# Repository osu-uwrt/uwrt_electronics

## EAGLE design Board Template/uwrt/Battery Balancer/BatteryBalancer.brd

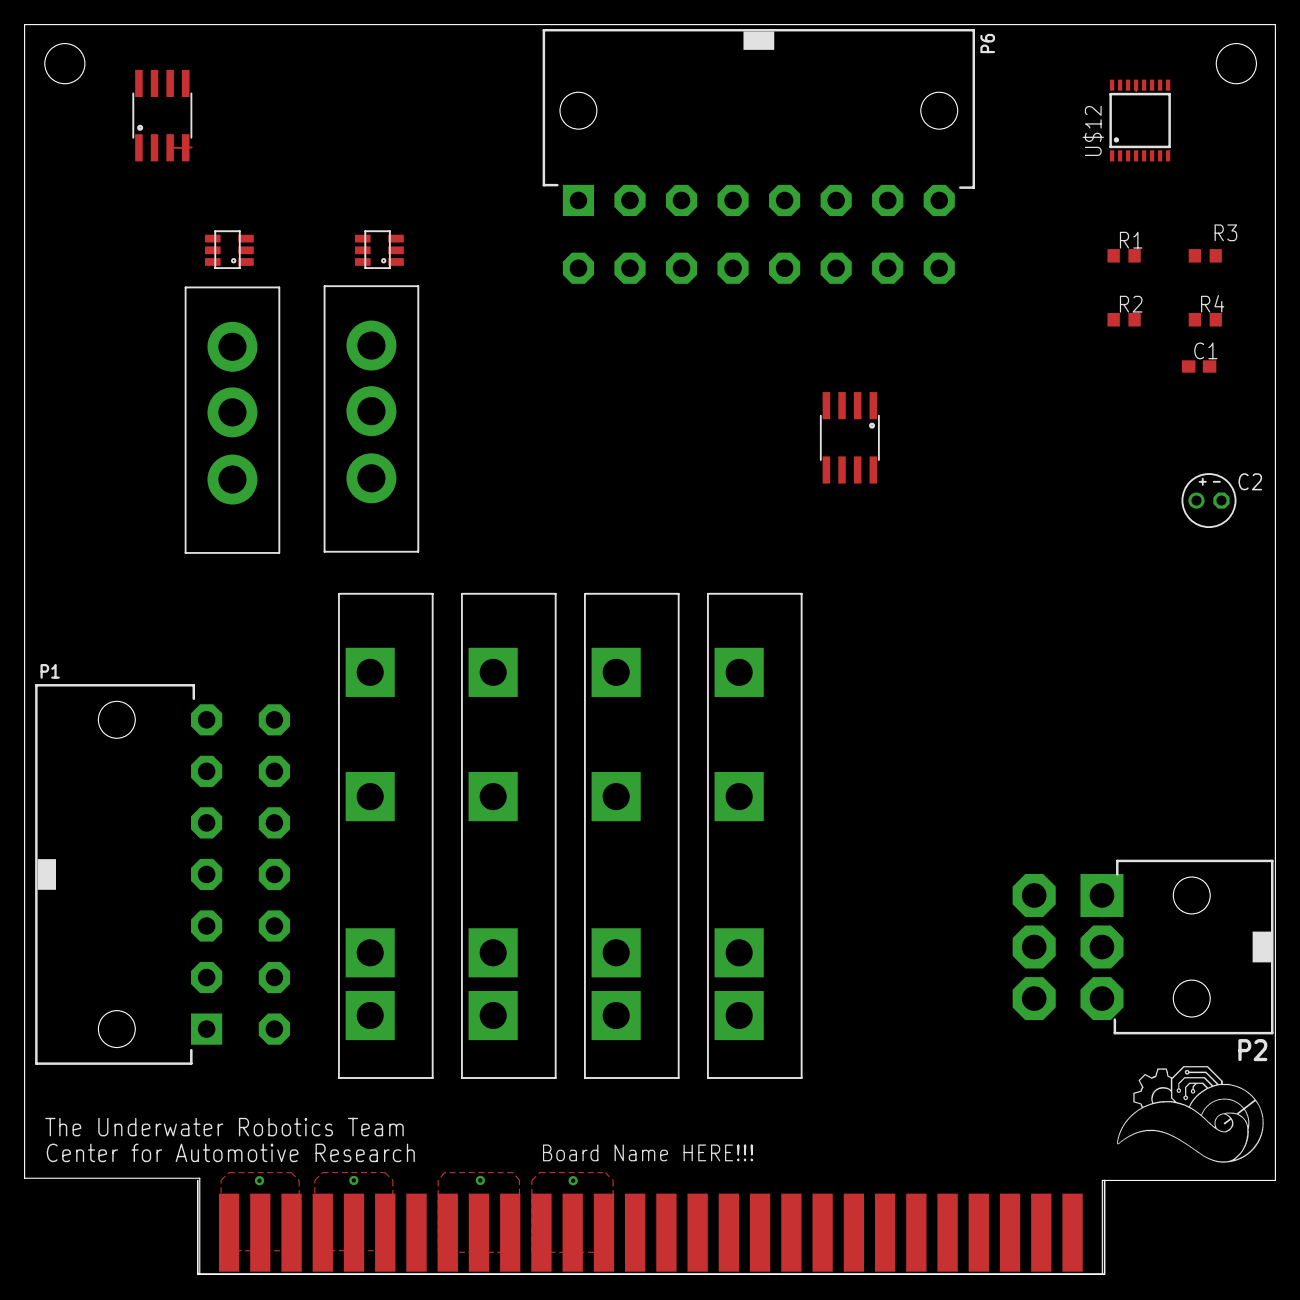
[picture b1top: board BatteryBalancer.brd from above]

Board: 2 copper layers, 101.7 x 101.6 mm, 21 parts (0 on the bottom side), 21 nets.

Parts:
C1: C0603
C2: E2-4
P1: 39-30-14?; 39-30-?14?
P2: 39-30-06?; 39-30-?06?
P6: 39-30-16?; 39-30-?16?
R1, R2, R3, R4: 100K; R0603
U$1: 5530843-EDGE; 5530843-6-BOARDFINGERS
U$2, U$3: LM5050
U$4, U$5: IXFX64N60P3
U$6, U$7: ACS722; SOIC-8
U$8, U$9, U$10, U$11: CMX60D20
U$12: ADC128D818; TSSOP-16

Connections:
+3V3: C1.1, C2.+, U$1.1, U$1.2, U$1.3, U$1.54, U$1.55, U$1.56, U$6.VCC, U$7.VCC, U$12.VREF
+5V: U$1.11, U$1.12, U$1.13, U$1.44, U$1.45, U$1.46
BALANCED_OUT: P2.1, P2.2, P2.3, U$2.1, U$2.6, U$3.1, U$3.6, U$4.DRAIN, U$5.DRAIN
GND: P1.8, P1.9, P1.10, P1.11, P1.12, P1.13, P1.14, P2.4, P2.5, P2.6, P6.9, P6.10, P6.11, P6.12, P6.13, P6.14, P6.15, P6.16, U$1.4, U$1.5, U$1.6, U$1.8, U$1.9, U$1.10, U$1.47, U$1.48, U$1.49, U$1.51, U$1.52, U$1.53, U$2.2, U$3.2, U$6.BW_SEL, U$6.GND, U$7.BW_SEL, U$7.GND, U$8.CONTROL-, U$9.CONTROL-, U$10.CONTROL-, U$11.CONTROL-
GNDA: C1.2, C2.-, R3.2, R4.2, U$12.GND
KILL_SWITCH: U$1.37, U$8.CONTROL+, U$9.CONTROL+, U$10.CONTROL+, U$11.CONTROL+
LOAD: U$8.LOAD+, U$9.LOAD+, U$10.LOAD+, U$11.LOAD+
MOTOR_POWER: P1.1, P1.2, P1.3, P1.4, P1.5, P1.6, P1.7, U$8.LOAD-, U$9.LOAD-
MOTOR_POWER2: U$10.LOAD-, U$11.LOAD-
unnamed: U$2.4, U$4.SOURCE, U$6.IP-1, U$6.IP-2
unnamed: U$2.5, U$4.GATE
unnamed: U$3.4, U$5.SOURCE, U$7.IP-1, U$7.IP-2
unnamed: U$3.5, U$5.GATE
unnamed: R1.2, R3.1, U$12.A0
unnamed: R1.1, R2.1, R2.2, R4.1, U$12.A1, U$12.V+
PORT_BATTERY: P6.5, P6.6, P6.7, P6.8, U$6.IP+1, U$6.IP+2
PORT_CURRENT: U$6.VIOUT, U$12.IN0
SENSOR_SCL: U$1.29, U$12.SCL
SENSOR_SDA: U$1.30, U$12.SDA
STBD_BATTERY: P6.1, P6.2, P6.3, P6.4, U$7.IP+1, U$7.IP+2
STBD_CURRENT: U$7.VIOUT, U$12.IN3

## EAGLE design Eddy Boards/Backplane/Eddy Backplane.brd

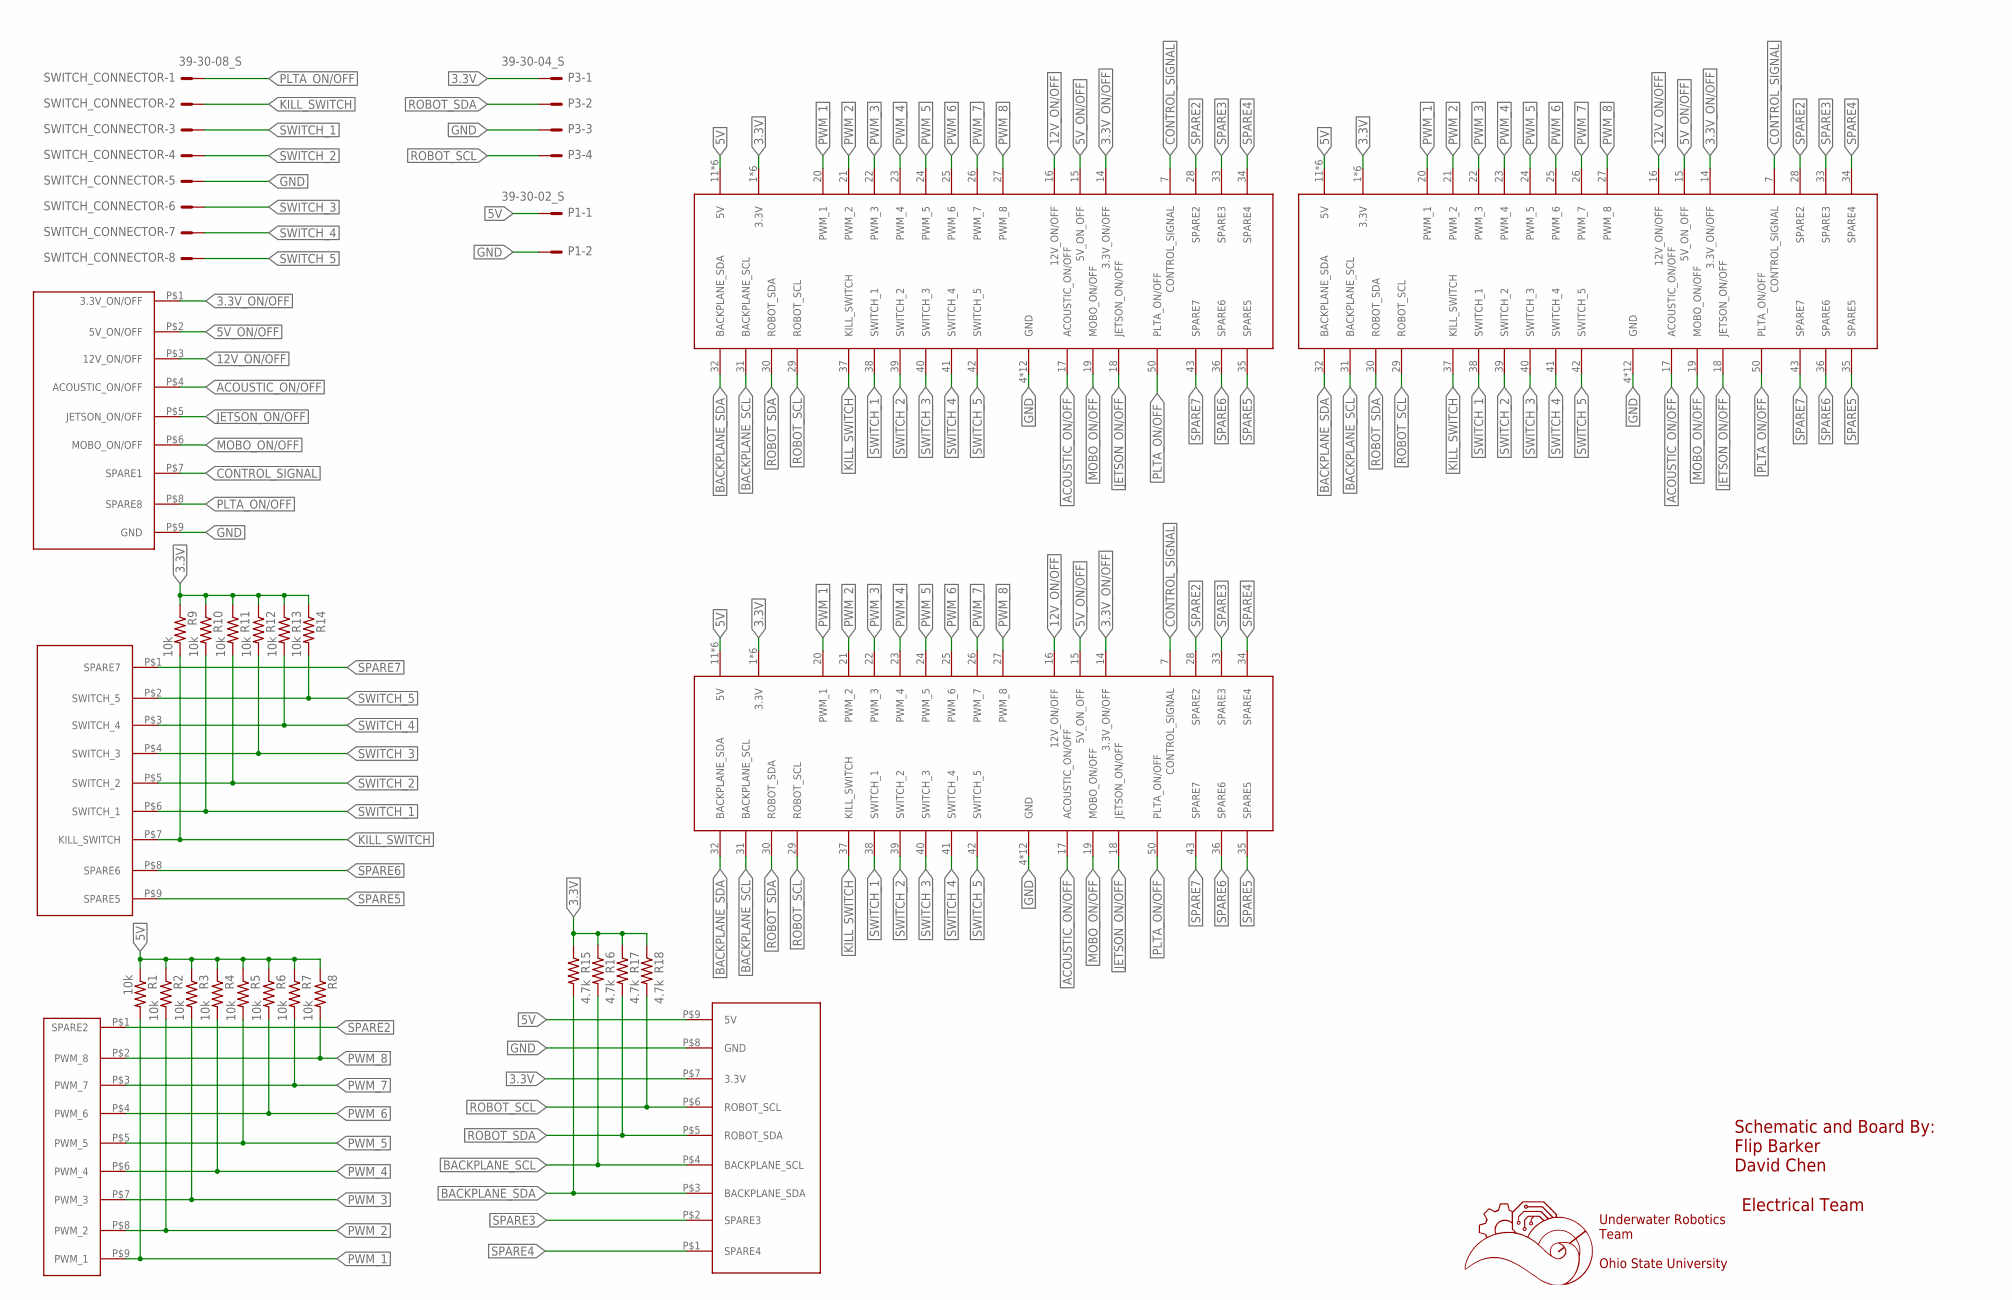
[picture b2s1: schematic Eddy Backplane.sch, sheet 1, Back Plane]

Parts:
P1: 39-30-02_S; 39-30-?02?
P3: 39-30-04_S; 39-30-?04?
PWR_ON: 929870-01-09_3; 929852-01-09_1ROW
R1, R2, R3, R4, R5, R6, R7, R8, R9, R10, R11, R12, R13, R14: 10k; R0603
R15, R16, R17, R18: 4.7k; R0603
SWITCH_CONN: 929870-01-09_1; 929852-01-09_1ROW
SWITCH_CONNECTOR: 39-30-08_S; 39-30-?08?
U$1, U$2, U$3: 5530843-FEMALE; 5530843-6-BACKPLANEMATE
U$6: 929870-01-09_2; 929852-01-09_1ROW
U$8: 929870-01-09_4; 929852-01-09_1ROW

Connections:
3.3V: P3.1, R9.1, R10.1, R11.1, R12.1, R13.1, R14.1, R15.1, R16.1, R17.1, R18.1, U$1.1 (3.3V), U$1.2 (3.3V), U$1.3 (3.3V), U$1.54 (3.3V), U$1.55 (3.3V), U$1.56 (3.3V), U$2.1 (3.3V), U$2.2 (3.3V), U$2.3 (3.3V), U$2.54 (3.3V), U$2.55 (3.3V), U$2.56 (3.3V), U$3.1 (3.3V), U$3.2 (3.3V), U$3.3 (3.3V), U$3.54 (3.3V), U$3.55 (3.3V), U$3.56 (3.3V), U$8.P$7 (3.3V); also elsewhere on the board
3.3V_ON/OFF: PWR_ON.P$1 (3.3V_ON/OFF), U$1.14 (3.3V_ON/OFF), U$2.14 (3.3V_ON/OFF), U$3.14 (3.3V_ON/OFF)
5V: P1.1, R1.1, R2.1, R3.1, R4.1, R5.1, R6.1, R7.1, R8.1, U$1.11 (5V), U$1.12 (5V), U$1.13 (5V), U$1.44 (5V), U$1.45 (5V), U$1.46 (5V), U$2.11 (5V), U$2.12 (5V), U$2.13 (5V), U$2.44 (5V), U$2.45 (5V), U$2.46 (5V), U$3.11 (5V), U$3.12 (5V), U$3.13 (5V), U$3.44 (5V), U$3.45 (5V), U$3.46 (5V), U$8.P$9 (5V); also elsewhere on the board
5V_ON/OFF: PWR_ON.P$2 (5V_ON/OFF), U$1.15 (5V_ON_OFF), U$2.15 (5V_ON_OFF), U$3.15 (5V_ON_OFF)
12V_ON/OFF: PWR_ON.P$3 (12V_ON/OFF), U$1.16 (12V_ON/OFF), U$2.16 (12V_ON/OFF), U$3.16 (12V_ON/OFF)
ACOUSTIC_ON/OFF: PWR_ON.P$4 (ACOUSTIC_ON/OFF), U$1.17 (ACOUSTIC_ON/OFF), U$2.17 (ACOUSTIC_ON/OFF), U$3.17 (ACOUSTIC_ON/OFF)
BACKPLANE_SCL: R16.2, U$1.31 (BACKPLANE_SCL), U$2.31 (BACKPLANE_SCL), U$3.31 (BACKPLANE_SCL), U$8.P$4 (BACKPLANE_SCL); also elsewhere on the board
BACKPLANE_SDA: R15.2, U$1.32 (BACKPLANE_SDA), U$2.32 (BACKPLANE_SDA), U$3.32 (BACKPLANE_SDA), U$8.P$3 (BACKPLANE_SDA); also elsewhere on the board
CONTROL_SIGNAL: PWR_ON.P$7 (SPARE1), U$1.7 (CONTROL_SIGNAL), U$2.7 (CONTROL_SIGNAL), U$3.7 (CONTROL_SIGNAL)
GND: P1.2, P3.3, PWR_ON.P$9 (GND), SWITCH_CONNECTOR.5, U$1.4 (GND), U$1.5 (GND), U$1.6 (GND), U$1.8 (GND), U$1.9 (GND), U$1.10 (GND), U$1.47 (GND), U$1.48 (GND), U$1.49 (GND), U$1.51 (GND), U$1.52 (GND), U$1.53 (GND), U$2.4 (GND), U$2.5 (GND), U$2.6 (GND), U$2.8 (GND), U$2.9 (GND), U$2.10 (GND), U$2.47 (GND), U$2.48 (GND), U$2.49 (GND), U$2.51 (GND), U$2.52 (GND), U$2.53 (GND), U$3.4 (GND), U$3.5 (GND), U$3.6 (GND), U$3.8 (GND), U$3.9 (GND), U$3.10 (GND), U$3.47 (GND), U$3.48 (GND), U$3.49 (GND), U$3.51 (GND), U$3.52 (GND), U$3.53 (GND), U$8.P$8 (GND); also elsewhere on the board
JETSON_ON/OFF: PWR_ON.P$5 (JETSON_ON/OFF), U$1.18 (JETSON_ON/OFF), U$2.18 (JETSON_ON/OFF), U$3.18 (JETSON_ON/OFF)
KILL_SWITCH: R9.2, SWITCH_CONN.P$7 (KILL_SWITCH), SWITCH_CONNECTOR.2, U$1.37 (KILL_SWITCH), U$2.37 (KILL_SWITCH), U$3.37 (KILL_SWITCH)
MOBO_ON/OFF: PWR_ON.P$6 (MOBO_ON/OFF), U$1.19 (MOBO_ON/OFF), U$2.19 (MOBO_ON/OFF), U$3.19 (MOBO_ON/OFF)
PLTA_ON/OFF: PWR_ON.P$8 (SPARE8), SWITCH_CONNECTOR.1, U$1.50 (PLTA_ON/OFF), U$2.50 (PLTA_ON/OFF), U$3.50 (PLTA_ON/OFF)
PWM_1: R1.2, U$1.20 (PWM_1), U$2.20 (PWM_1), U$3.20 (PWM_1), U$6.P$9 (PWM_1); also elsewhere on the board
PWM_2: R2.2, U$1.21 (PWM_2), U$2.21 (PWM_2), U$3.21 (PWM_2), U$6.P$8 (PWM_2); also elsewhere on the board
PWM_3: R3.2, U$1.22 (PWM_3), U$2.22 (PWM_3), U$3.22 (PWM_3), U$6.P$7 (PWM_3); also elsewhere on the board
PWM_4: R4.2, U$1.23 (PWM_4), U$2.23 (PWM_4), U$3.23 (PWM_4), U$6.P$6 (PWM_4); also elsewhere on the board
PWM_5: R5.2, U$1.24 (PWM_5), U$2.24 (PWM_5), U$3.24 (PWM_5), U$6.P$5 (PWM_5); also elsewhere on the board
PWM_6: R6.2, U$1.25 (PWM_6), U$2.25 (PWM_6), U$3.25 (PWM_6), U$6.P$4 (PWM_6); also elsewhere on the board
PWM_7: R7.2, U$1.26 (PWM_7), U$2.26 (PWM_7), U$3.26 (PWM_7), U$6.P$3 (PWM_7); also elsewhere on the board
PWM_8: R8.2, U$1.27 (PWM_8), U$2.27 (PWM_8), U$3.27 (PWM_8), U$6.P$2 (PWM_8); also elsewhere on the board
ROBOT_SCL: P3.4, R18.2, U$1.29 (ROBOT_SCL), U$2.29 (ROBOT_SCL), U$3.29 (ROBOT_SCL), U$8.P$6 (ROBOT_SCL); also elsewhere on the board
ROBOT_SDA: P3.2, R17.2, U$1.30 (ROBOT_SDA), U$2.30 (ROBOT_SDA), U$3.30 (ROBOT_SDA), U$8.P$5 (ROBOT_SDA); also elsewhere on the board
SPARE2: U$1.28 (SPARE2), U$2.28 (SPARE2), U$3.28 (SPARE2), U$6.P$1 (SPARE2)
SPARE3: U$1.33 (SPARE3), U$2.33 (SPARE3), U$3.33 (SPARE3), U$8.P$2 (SPARE3)
SPARE4: U$1.34 (SPARE4), U$2.34 (SPARE4), U$3.34 (SPARE4), U$8.P$1 (SPARE4)
SPARE5: SWITCH_CONN.P$9 (SPARE5), U$1.35 (SPARE5), U$2.35 (SPARE5), U$3.35 (SPARE5)
SPARE6: SWITCH_CONN.P$8 (SPARE6), U$1.36 (SPARE6), U$2.36 (SPARE6), U$3.36 (SPARE6)
SPARE7: SWITCH_CONN.P$1 (SPARE7), U$1.43 (SPARE7), U$2.43 (SPARE7), U$3.43 (SPARE7)
SWITCH_1: R10.2, SWITCH_CONN.P$6 (SWITCH_1), SWITCH_CONNECTOR.3, U$1.38 (SWITCH_1), U$2.38 (SWITCH_1), U$3.38 (SWITCH_1)
SWITCH_2: R11.2, SWITCH_CONN.P$5 (SWITCH_2), SWITCH_CONNECTOR.4, U$1.39 (SWITCH_2), U$2.39 (SWITCH_2), U$3.39 (SWITCH_2)
SWITCH_3: R12.2, SWITCH_CONN.P$4 (SWITCH_3), SWITCH_CONNECTOR.6, U$1.40 (SWITCH_3), U$2.40 (SWITCH_3), U$3.40 (SWITCH_3)
SWITCH_4: R13.2, SWITCH_CONN.P$3 (SWITCH_4), SWITCH_CONNECTOR.7, U$1.41 (SWITCH_4), U$2.41 (SWITCH_4), U$3.41 (SWITCH_4)
SWITCH_5: R14.2, SWITCH_CONN.P$2 (SWITCH_5), SWITCH_CONNECTOR.8, U$1.42 (SWITCH_5), U$2.42 (SWITCH_5), U$3.42 (SWITCH_5)

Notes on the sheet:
Underwater Robotics Team Ohio State University
Electrical Team
Schematic and Board By: Flip Barker David Chen

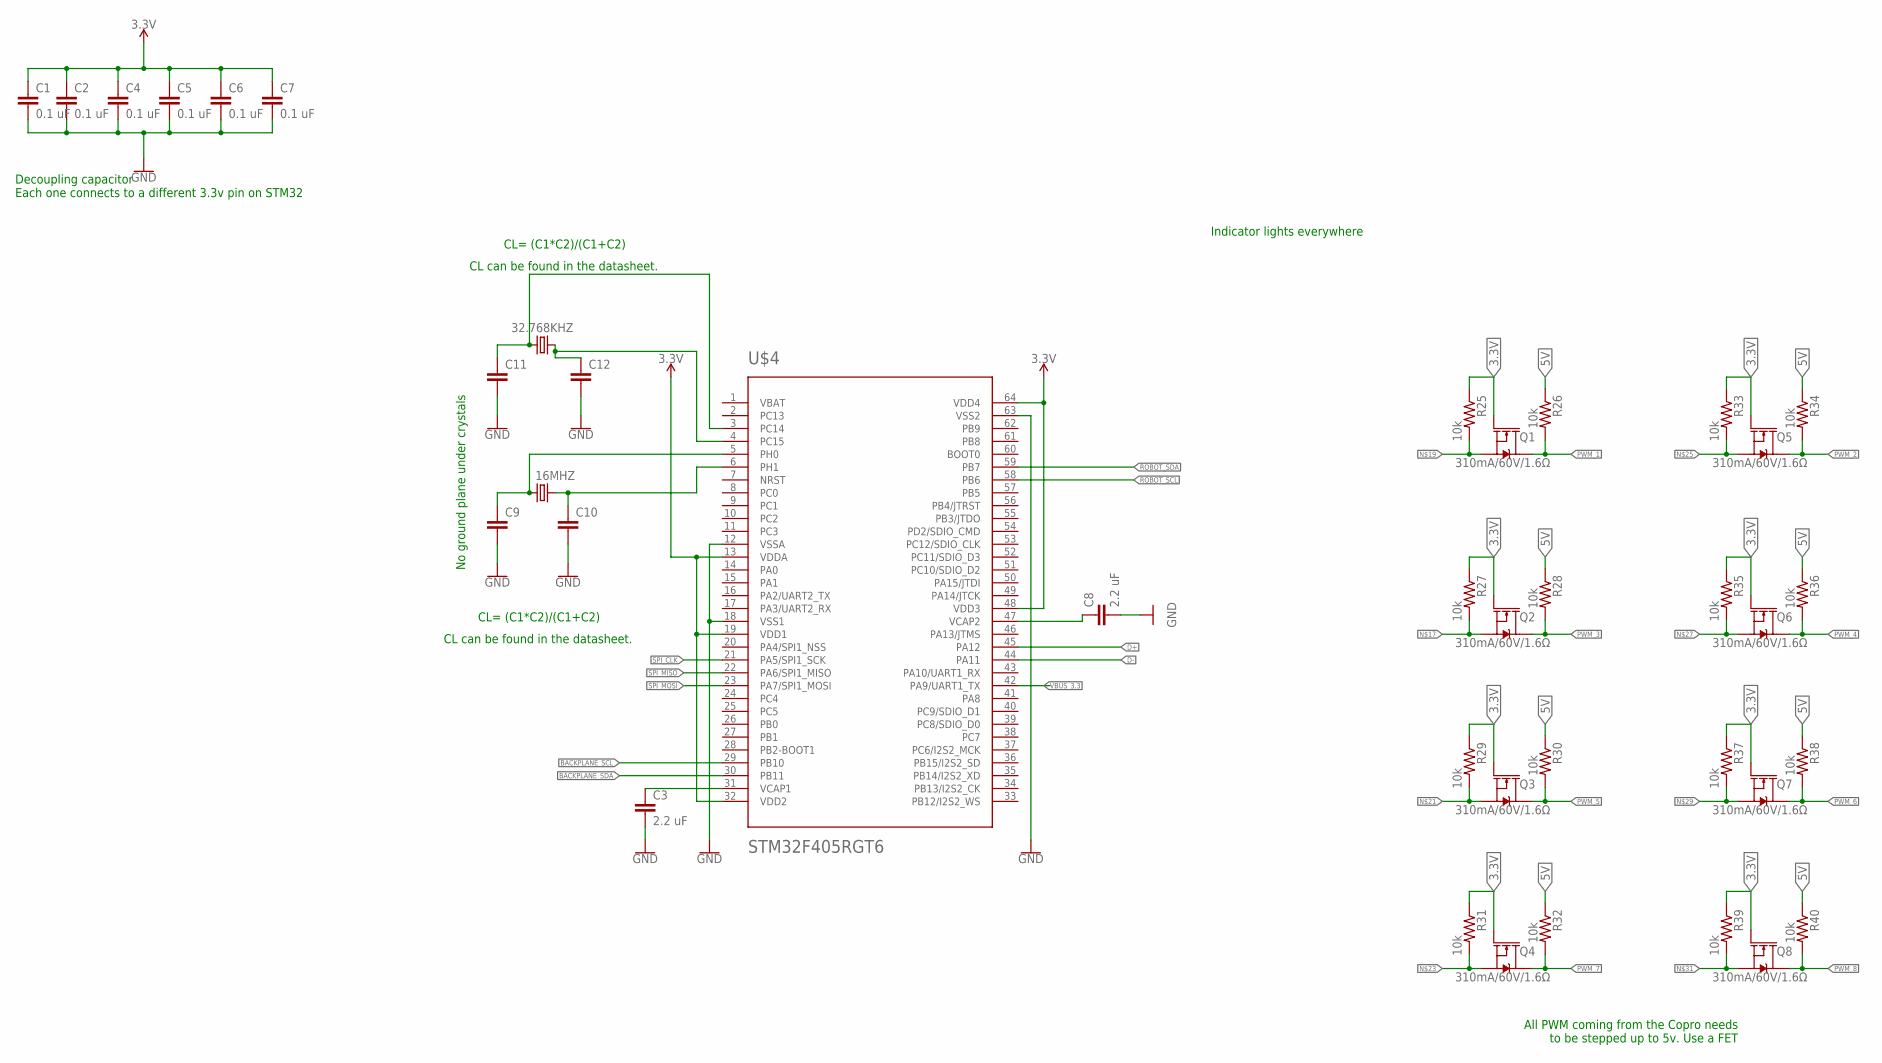
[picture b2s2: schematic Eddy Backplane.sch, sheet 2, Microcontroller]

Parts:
16MHZ, 32.768KHZ: CRYSTALPTH-HC49US; HC49US
C1, C2, C4, C5, C6, C7: 0.1 uF; C0603
C3, C8: 2.2 uF; C0603
C9, C10, C11, C12: C-EUC0603; C0603
Q1, Q2, Q3, Q4, Q5, Q6, Q7, Q8: 310mA/60V/1.6Ω; SOT323
R25, R26, R27, R28, R29, R30, R31, R32, R33, R34, R35, R36, R37, R38, R39, R40: 10k; R0603
U$4: STM32F405RGT6; TQFP64

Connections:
3.3V: C1.1, C2.1, C4.1, C5.1, C6.1, C7.1, Q1.1 (G), Q2.1 (G), Q3.1 (G), Q4.1 (G), Q5.1 (G), Q6.1 (G), Q7.1 (G), Q8.1 (G), R25.1, R27.1, R29.1, R31.1, R33.1, R35.1, R37.1, R39.1, U$4.13 (VDDA), U$4.19 (VDD1), U$4.32 (VDD2), U$4.48 (VDD3), U$4.64 (VDD4); also elsewhere on the board
5V: R26.1, R28.1, R30.1, R32.1, R34.1, R36.1, R38.1, R40.1; also elsewhere on the board
BACKPLANE_SCL: U$4.29 (PB10); also elsewhere on the board
BACKPLANE_SDA: U$4.30 (PB11); also elsewhere on the board
D+: U$4.45 (PA12); also elsewhere on the board
D-: U$4.44 (PA11); also elsewhere on the board
GND: C1.2, C2.2, C3.2, C4.2, C5.2, C6.2, C7.2, C8.2, C9.2, C10.2, C11.2, C12.2, U$4.12 (VSSA), U$4.18 (VSS1), U$4.63 (VSS2); also elsewhere on the board
unnamed: C3.1, U$4.31 (VCAP1)
unnamed: C8.1, U$4.47 (VCAP2)
unnamed: 32.768KHZ.1, C11.1, U$4.3 (PC14)
unnamed: 16MHZ.1, C9.1, U$4.5 (PH0)
unnamed: 32.768KHZ.2, C12.1, U$4.4 (PC15)
unnamed: 16MHZ.2, C10.1, U$4.6 (PH1)
unnamed: Q2.2 (S), R27.2
unnamed: Q1.2 (S), R25.2
unnamed: Q3.2 (S), R29.2
unnamed: Q4.2 (S), R31.2
unnamed: Q5.2 (S), R33.2
unnamed: Q6.2 (S), R35.2
unnamed: Q7.2 (S), R37.2
unnamed: Q8.2 (S), R39.2
PWM_1: Q1.3 (D), R26.2; also elsewhere on the board
PWM_2: Q5.3 (D), R34.2; also elsewhere on the board
PWM_3: Q2.3 (D), R28.2; also elsewhere on the board
PWM_4: Q6.3 (D), R36.2; also elsewhere on the board
PWM_5: Q3.3 (D), R30.2; also elsewhere on the board
PWM_6: Q7.3 (D), R38.2; also elsewhere on the board
PWM_7: Q4.3 (D), R32.2; also elsewhere on the board
PWM_8: Q8.3 (D), R40.2; also elsewhere on the board
ROBOT_SCL: U$4.58 (PB6); also elsewhere on the board
ROBOT_SDA: U$4.59 (PB7); also elsewhere on the board
SPI_CLK: U$4.21 (PA5/SPI1_SCK); also elsewhere on the board
SPI_MISO: U$4.22 (PA6/SPI1_MISO); also elsewhere on the board
SPI_MOSI: U$4.23 (PA7/SPI1_MOSI); also elsewhere on the board
VBUS_3.3: U$4.42 (PA9/UART1_TX); also elsewhere on the board

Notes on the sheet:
CL= (C1*C2)/(C1+C2)
No ground plane under crystals
CL can be found in the datasheet.
Decoupling capacitor Each one connects to a different 3.3v pin on STM32
Indicator lights everywhere
All PWM coming from the Copro needs to be stepped up to 5v. Use a FET

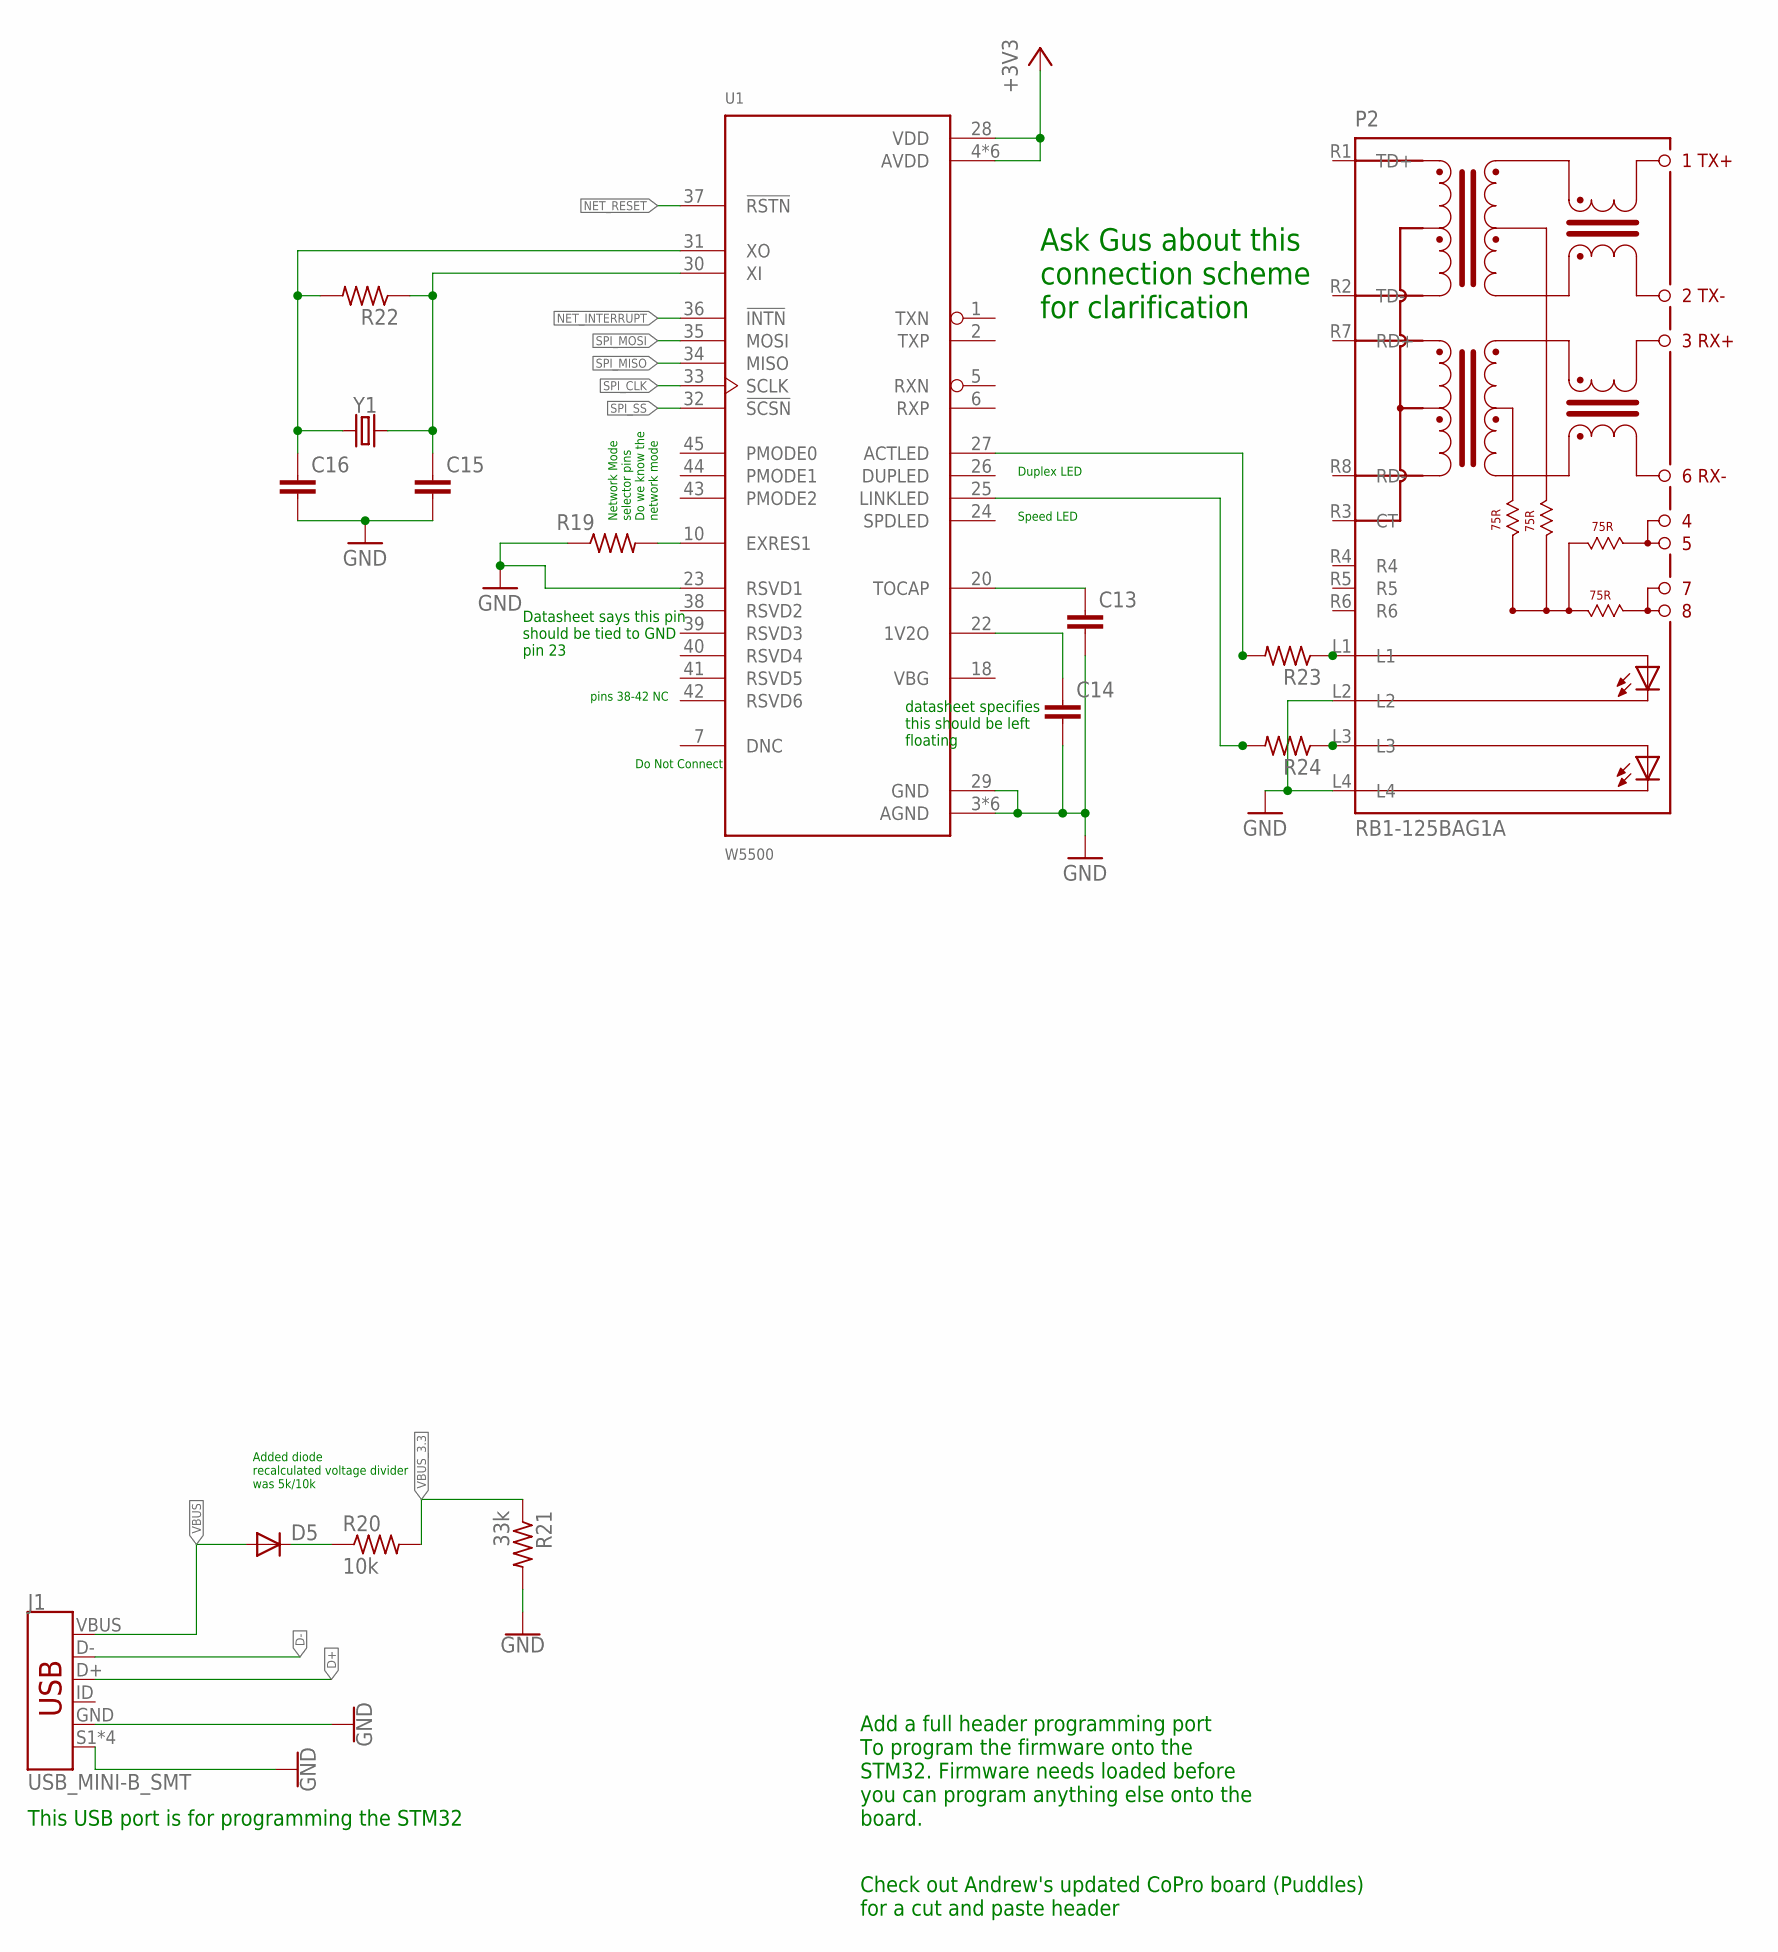
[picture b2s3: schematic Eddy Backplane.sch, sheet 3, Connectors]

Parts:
C13, C14, C15, C16: C-EUC0603; C0603
D5: DIODE-SMB; SMB
J1: USB_MINI-B_SMT; USB-MINIB
P2: RB1-125BAG1A; WIZNET_RB1-125BAG1A
R19, R22, R23, R24: R-US_R0603; R0603
R20: 10k; R0603
R21: 33k; R0603
U1: W5500; QFP50P900X900X160-48N
Y1: CRYSTALPTH-HC49US; HC49US

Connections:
+3V3: U1.4 (AVDD), U1.8 (AVDD), U1.11 (AVDD), U1.15 (AVDD), U1.17 (AVDD), U1.21 (AVDD), U1.28 (VDD)
D+: J1.D+; also elsewhere on the board
D-: J1.D-; also elsewhere on the board
GND: C13.2, C14.2, C15.2, C16.2, J1.GND, J1.S1 (SHIELD), J1.S2 (SHIELD), J1.S3 (SHIELD), J1.S4 (SHIELD), P2.L2, P2.L4, R19.1, R21.2, U1.3 (AGND), U1.9 (AGND), U1.14 (AGND), U1.16 (AGND), U1.19 (AGND), U1.23 (RSVD1), U1.29 (GND), U1.48 (AGND); also elsewhere on the board
unnamed: C14.1, U1.22 (1V2O)
unnamed: D5.C, R20.1
unnamed: C15.1, R22.1, U1.30 (XI), Y1.2
unnamed: C16.1, R22.2, U1.31 (XO), Y1.1
unnamed: R24.2, U1.25 (LINKLED)
unnamed: R23.2, U1.27 (ACTLED)
unnamed: C13.1, U1.20 (TOCAP)
unnamed: R19.2, U1.10 (EXRES1)
unnamed: P2.L1, R23.1
unnamed: P2.L3, R24.1
NET_INTERRUPT: U1.36 (!INTN)
NET_RESET: U1.37 (!RSTN)
SPI_CLK: U1.33 (SCLK); also elsewhere on the board
SPI_MISO: U1.34 (MISO); also elsewhere on the board
SPI_MOSI: U1.35 (MOSI); also elsewhere on the board
SPI_SS: U1.32 (!SCSN)
VBUS: D5.A, J1.VBUS
VBUS_3.3: R20.2, R21.1; also elsewhere on the board

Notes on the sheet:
This USB port is for programming the STM32
Add a full header programming port To program the firmware onto the STM32. Firmware needs loaded before you can program anything else onto the board.
Check out Andrew's updated CoPro board (Puddles) for a cut and paste header
datasheet specifies this should be left floating
Datasheet says this pin should be tied to GND pin 23
pins 38-42 NC
Do Not Connect
Duplex LED
Speed LED
Network Mode selector pins Do we know the network mode
Added diode recalculated voltage divider was 5k/10k
Ask Gus about this connection scheme for clarification

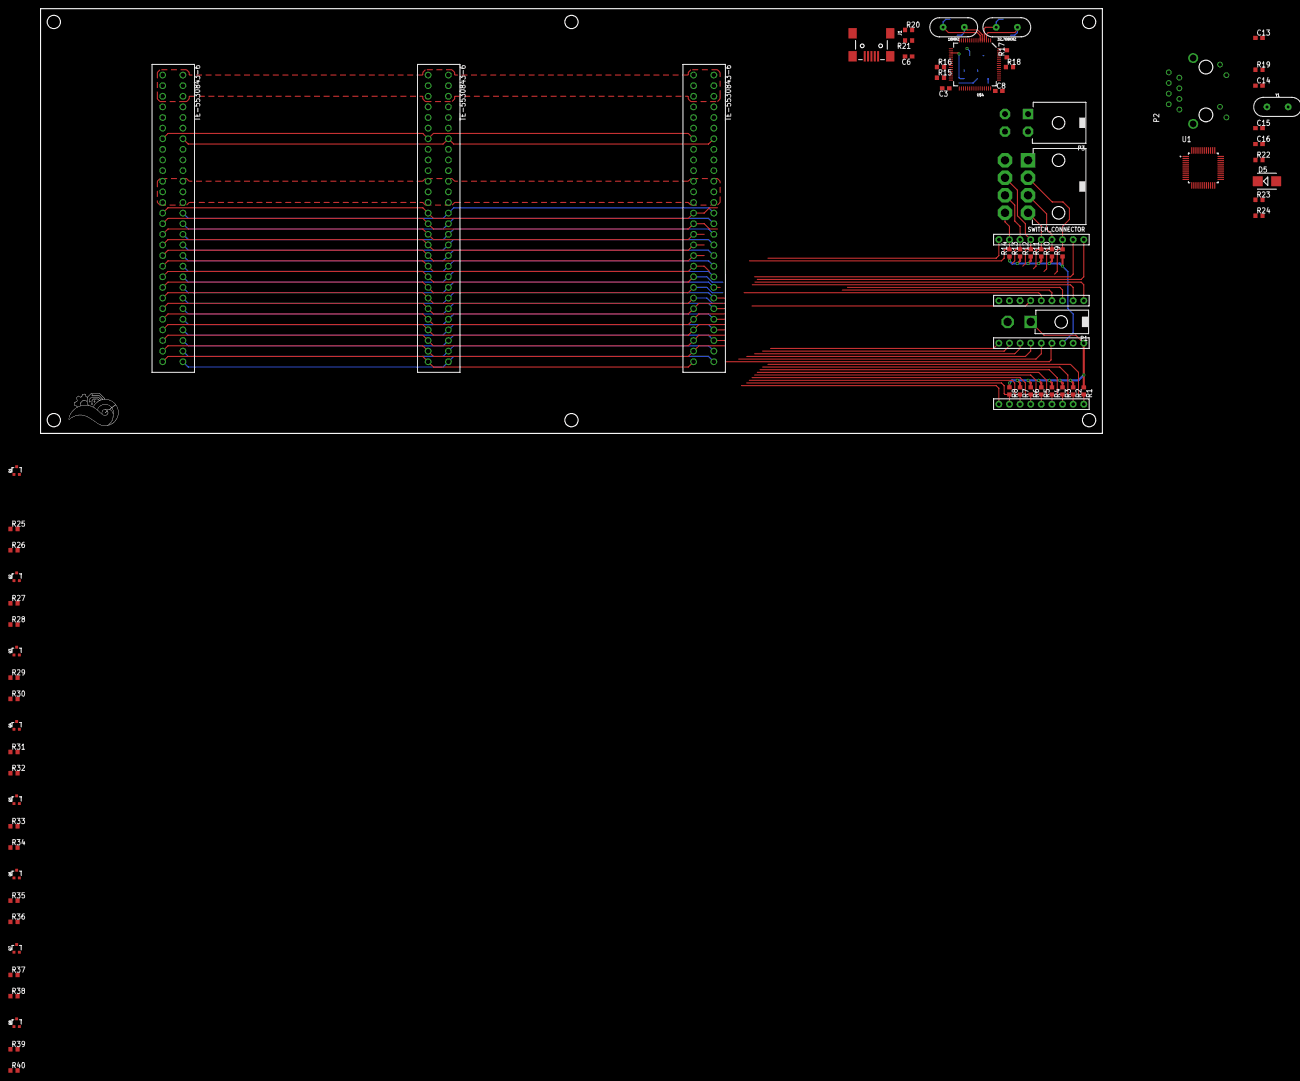
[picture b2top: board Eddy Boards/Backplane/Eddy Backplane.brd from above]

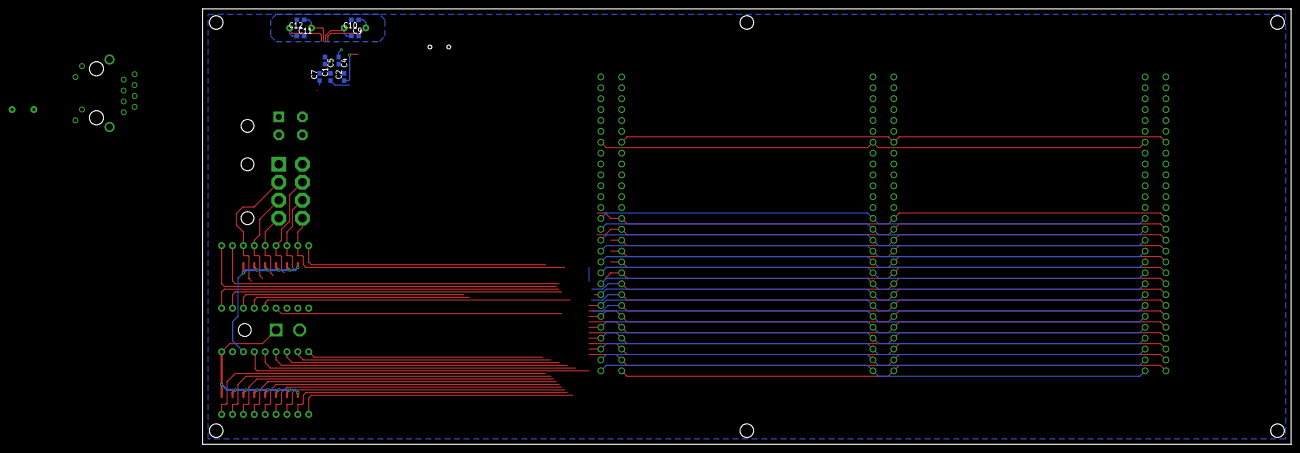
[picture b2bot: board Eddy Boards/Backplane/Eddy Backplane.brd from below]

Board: 2 copper layers, 254.0 x 101.6 mm, 82 parts (9 on the bottom side), 67 nets.

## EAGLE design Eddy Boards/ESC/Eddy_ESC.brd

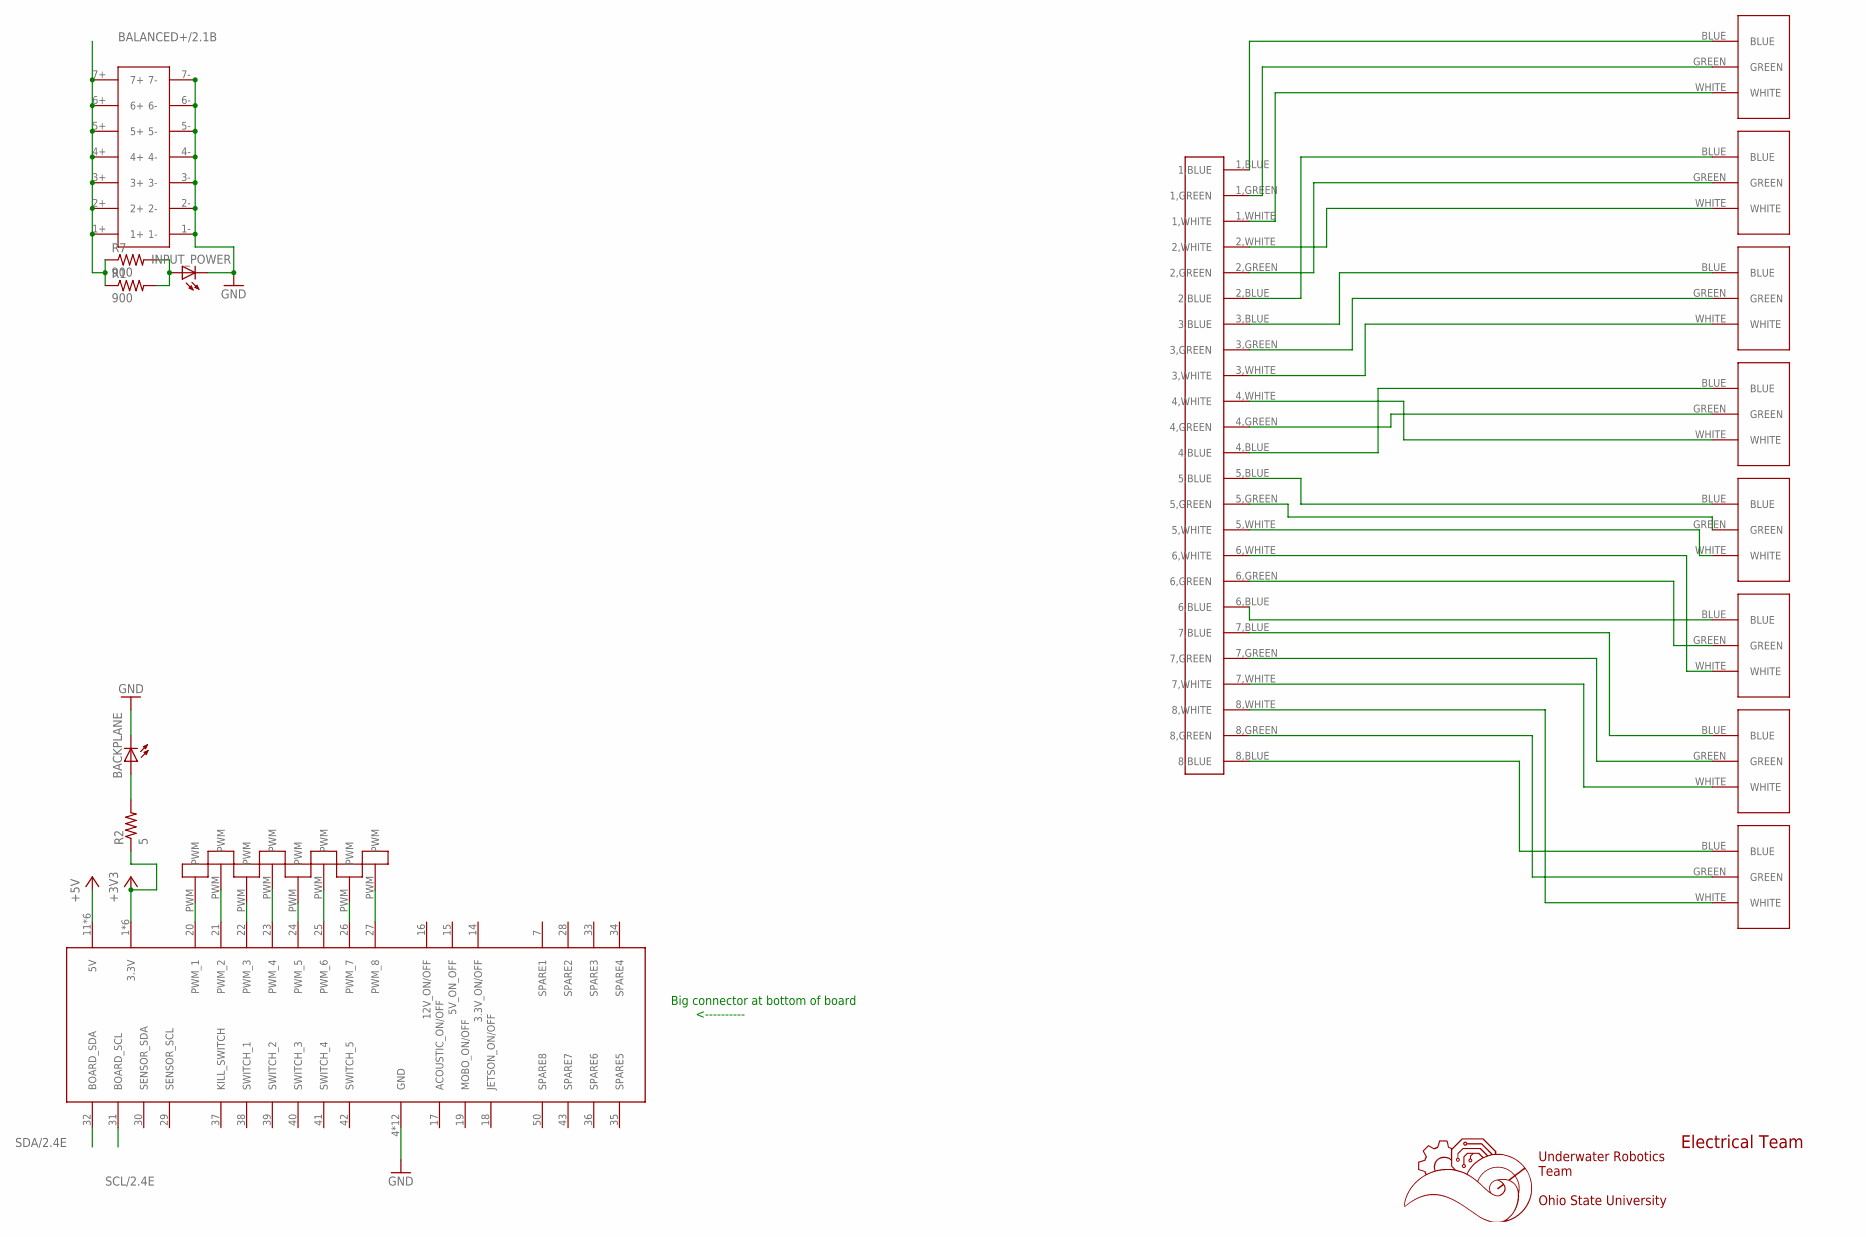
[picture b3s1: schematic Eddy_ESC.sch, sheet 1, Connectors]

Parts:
BACKPLANE: LEDCHIPLED_0603; CHIPLED_0603
INPUT_POWER: LEDCHIPLED_0603; CHIPLED_0603
R1, R7: 900; R0603
R2: 5; R0603
U$1: 5530843-EDGE; 5530843-6-BOARDFINGERS
U$2, U$3, U$4, U$5, U$6, U$7, U$8, U$9: 1711738
U$10: 24PINCONVERTER
U$11: 14PIN_VERT
U$12, U$13, U$14, U$15, U$16, U$17, U$18, U$19: MALE1PINHEADER

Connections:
+3V3: R2.1, U$1.1 (3.3V), U$1.2 (3.3V), U$1.3 (3.3V), U$1.54 (3.3V), U$1.55 (3.3V), U$1.56 (3.3V); also elsewhere on the board
+5V: U$1.11 (5V), U$1.12 (5V), U$1.13 (5V), U$1.44 (5V), U$1.45 (5V), U$1.46 (5V)
BALANCED+/2.1B: R1.1, R7.1, U$11.1+, U$11.2+, U$11.3+, U$11.4+, U$11.5+, U$11.6+, U$11.7+
unnamed: U$9.BLUE, U$10.1,BLUE
unnamed: U$9.GREEN, U$10.1,GREEN
unnamed: U$9.WHITE, U$10.1,WHITE
unnamed: U$2.BLUE, U$10.2,BLUE
unnamed: U$2.WHITE, U$10.2,WHITE
unnamed: U$2.GREEN, U$10.2,GREEN
unnamed: U$3.BLUE, U$10.3,BLUE
unnamed: U$3.GREEN, U$10.3,GREEN
unnamed: U$3.WHITE, U$10.3,WHITE
unnamed: U$4.BLUE, U$10.4,BLUE
unnamed: U$4.GREEN, U$10.4,GREEN
unnamed: U$4.WHITE, U$10.4,WHITE
unnamed: U$5.BLUE, U$10.5,BLUE
unnamed: U$5.GREEN, U$10.5,GREEN
unnamed: U$5.WHITE, U$10.5,WHITE
unnamed: U$6.WHITE, U$10.6,WHITE
unnamed: U$6.GREEN, U$10.6,GREEN
unnamed: U$6.BLUE, U$10.6,BLUE
unnamed: U$7.BLUE, U$10.7,BLUE
unnamed: U$7.GREEN, U$10.7,GREEN
unnamed: U$7.WHITE, U$10.7,WHITE
unnamed: U$8.WHITE, U$10.8,WHITE
unnamed: U$8.GREEN, U$10.8,GREEN
unnamed: U$8.BLUE, U$10.8,BLUE
unnamed: U$1.20 (PWM_1), U$12.PWM
unnamed: U$1.21 (PWM_2), U$13.PWM
unnamed: U$1.22 (PWM_3), U$14.PWM
unnamed: U$1.23 (PWM_4), U$16.PWM
unnamed: U$1.24 (PWM_5), U$15.PWM
unnamed: U$1.25 (PWM_6), U$17.PWM
unnamed: U$1.26 (PWM_7), U$18.PWM
unnamed: U$1.27 (PWM_8), U$19.PWM
unnamed: INPUT_POWER.A, R1.2, R7.2
unnamed: BACKPLANE.A, R2.2
SCL/2.4E: U$1.31 (BOARD_SCL)
SDA/2.4E: U$1.32 (BOARD_SDA)

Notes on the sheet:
Underwater Robotics Team Ohio State University
Electrical Team
Big connector at bottom of board <----------

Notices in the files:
parts and their libraries:
con-molex-mini-fit: Copyright (C) 2011, Bob Starr
SparkFun-Clocks: Licensing: Creative Commons ShareAlike 4.0 International - https://creativecommons.org/licenses/by-sa/4.0
